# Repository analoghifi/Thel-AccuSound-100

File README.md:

# Thel AccuSound 100
Thel AccuSound 100 audio power amplifier module (mono single channel)  
using vertical MOSFETs (often generalised as "[HEXFET](https://sound-au.com/articles/hexfet.htm)s")
* RMS power output from 20W up to 500W\* (1000W\*\*) | 7Hz...1,5MHz [-3dB]  |  0,4µs
* Class-A-Mode possible | Bridge Mode possible  
* unbalanced (single-ended/asymmetrical) audio input  
* not DC-coupled (has an input Cap (KP film/foil))  
* using vertical MOSFETs IRFP240 / IRFP9240  
* integrated (DC-) protection & anti-pop delay -circuit with relays
  
\*(depends on the supply voltage only)  
\*\*(bridge mode and short time only ➔ see <a href="/docs/4.) final version 2003-2015/power_output_table_version_2003-2015.png">Table 1</a> / <a href="/docs/3) version 1995-2003/power_output_table_version_1995-2003__V2.jpg">Table 2</a>)  
  
#### changes from "3) version 1995-2003" *[AccuSound Pro]* to "4) final version 2003-2015" *[AccuSound 100]*:  
* introducing source resistors (for better stability / better thermal behaviour / better currenct and load sharing)
* therefore reduced power output (compare <a href="/docs/3) version 1995-2003/power_output_table_version_1995-2003__V2.jpg">old</a> with <a href="/docs/4.) final version 2003-2015/power_output_table_version_2003-2015.png">new</a>)
* slightly different schematic (compare <a href="/hardware/3) version 1995-2003/accusound_version_1995-2003_schematic_V1.jpg">old</a> with <a href="/hardware/4.) final version 2003-2015/AccuSound_100_schematic_2004__corrected.jpg">new</a>)
* different pcb layout
* in the middle of 2010: replacement of the 2 very good tungsten-silver double (two-step)\*\*\* contact relays (erosion-resistant) with 2 normal "high-current" relays (Schrack RP3SL024)  
* replacing almost all foil caps (including the input cap) with the very good CDE film/foil KP-caps (<a href="https://github.com/analoghifi/capacitors/blob/main/audio%20and%20filter%20capacitors/docs/datasheets/kp/CDE_series_WPP.pdf">WPP-Series</a>)
* introducing silver mica bypass caps at some sensible places in the circuit
  
\*\*\*(see here -> <a href="/docs/components datasheets/special relay version 1995-2003">Relay type: Hengstler H-550-1759"</a>)
  
.
  
## last 4.x) version sold from 2003 til 2015:  

https://web.archive.org/web/20071014012558/http://www.thel-audioworld.de/module/acuso/acuso.htm  
https://web.archive.org/web/20120130132153/http://thel-audioworld.de/module/acuso/acuso.htm  
https://web.archive.org/web/20150216004915/http://www.thel-audioworld.de/module/acuso/acuso.htm  
  
## older 3) version sold from 1995 til 2003:  

https://web.archive.org/web/20020608091959/http://thel-audioworld.de:80/module/acuso/acuso.htm  

----  
### Kicad projects in this repo:  
* [version 2006-2011](https://github.com/analoghifi/Thel-AccuSound-100/tree/main/hardware/4.\)%20final%20version%202003-2015/4.2\)%20version%202006-2011/KiCad/original) | state: initial release v1.01 | like the original, 1-layer, THT
* [version 2011-2015](https://github.com/analoghifi/Thel-AccuSound-100/tree/main/hardware/4.\)%20final%20version%202003-2015/4.3\)%20version%202011-2015/KiCad/original) | state: coming soon... | like the original, 1-layer, THT

----

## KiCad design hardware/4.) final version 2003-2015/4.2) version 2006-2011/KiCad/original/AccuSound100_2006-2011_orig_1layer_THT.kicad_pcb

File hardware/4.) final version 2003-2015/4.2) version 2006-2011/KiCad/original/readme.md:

#### work in progress not finished yet !  

this is not the original Thel PCB but it's very like\* the original with the following exceptions:  
* different board dimensions original: 200mm x 100mm -> this PCB: 200mm x 103mm  
* using a combined 5.0mm/7.5mm pin spacing footprint for the small foil caps C12 and C23
* using a combined 3.5mm/5.0mm/5.9mm/7.5mm pin spacing footprint for the Mica caps C2, C3 and C9 (see below)  
  
\*(same schematic / same 1-layer\** layout THT / same THT components in the same places on the board)  
\**(strictly speaking, this KiCad PCB is a two-layer PCB with plated-through holes, but you can also (let) produce it as a classic 1-layer PCB with non-plated holes if you wish, since all the tracks are on the bottom side only)  
  
----  

### remarks:  
#### C2,C3,C9: 
in the original, Mica capacitors from the US company "Cornell Dubilier Electronics" (CDE) are used for C2, C3 and C9  
the [CD15-Series](https://github.com/analoghifi/capacitors/blob/main/audio%20and%20filter%20capacitors/docs/datasheets/mica%20glimmer/CDE_Silver_Mica_series_STD-DIPPED.pdf) or the better [CD17 Series](https://github.com/analoghifi/capacitors/blob/main/audio%20and%20filter%20capacitors/docs/datasheets/mica%20glimmer/CDE_Series_CD17_CD18_high_frequency.pdf) is used:  
* C2, C3 = 47pF / 1% / 500V / 5.9mm pitch / Type-No. CD15ED470FO3 ([stock at Mouser](https://www2.mouser.com/ProductDetail/Cornell-Dubilier-CDE/CD15ED470FO3?qs=9iVfQKk8ifFmXLRqX5bCNQ%3D%3D))  
or better CD17ED470JO3F ([stock at Mouser](https://www2.mouser.com/ProductDetail/Cornell-Dubilier-CDE/CD17ED470JO3F?qs=nnhpPVbCybXjnSWSlsUlRA%3D%3D))
* C9 = 10pF / 5% / 500V / 5.9mm pitch / Type-No. CD15CD100JO3 ([stock at Mouser](https://www2.mouser.com/ProductDetail/Cornell-Dubilier-CDE/CD15CD100JO3?qs=m9iv7GyUMnFXRIC2%252BbnrrQ%3D%3D))  
or better CD17CD100JO3F ([stock at Mouser](https://www2.mouser.com/ProductDetail/Cornell-Dubilier-CDE/CD17CD100JO3F?qs=PXF%252Blbo4VJ7Sv5GDGZWsoQ%3D%3D))

Alternatively:  
since C2,C3 and C9 are used for controlling the ultrasonic frequencies (>20kHz) here in this circuit you may use instead  
ceramic C0G capacitors (tolerance: 1% to 2,5% / rated DC Voltage: 100V or 250V / pitch 5mm or 7,5mm)  
e.g. KEMET "[goldmax 300](https://github.com/analoghifi/capacitors/blob/main/audio%20and%20filter%20capacitors/docs/datasheets/C0G/KEMET_C1049_GOLDMAX_C0G_THT.pdf)" Series in THT version ([10pF/47pF stock at mouser](https://www2.mouser.com/c/passive-components/capacitors/ceramic-capacitors/mlccs-multilayer-ceramic-capacitors/multilayer-ceramic-capacitors-mlcc-leaded/?q=goldmax&capacitance=10%20pF%7C~47%20pF&dielectric=C0G%20%28NP0%29&lead%20spacing=5.08%20mm&tolerance=1%20%25&voltage%20rating%20dc=250%20VDC))  
They perform very well for high frequencies and are a very good alternative to the expensive Mica caps from CDE.  
The dielectric material is important here: Do NOT use ceramic capacitors with a dielectric other than C0G (NP0) !  
  
The footprint on my PCB is prepared for both pitches:  
the odd 5.9mm for the Micas as well as 3.5mm / 5.0mm or 7.5mm for alternative capacitors  
 
----  
  
these are KiCad 6.x projects  
see how to get the proper 3D-Models from here: https://github.com/analoghifi/KiCad-3D-Models  
  
----  
  
use kicanvas.org to see this KiCad-Project in Browser:  
https://kicanvas.org/?github=https://github.com/analoghifi/Thel-AccuSound-100/tree/main/hardware/4.)%20final%20version%202003-2015/4.2)%20version%202006-2011/KiCad/original

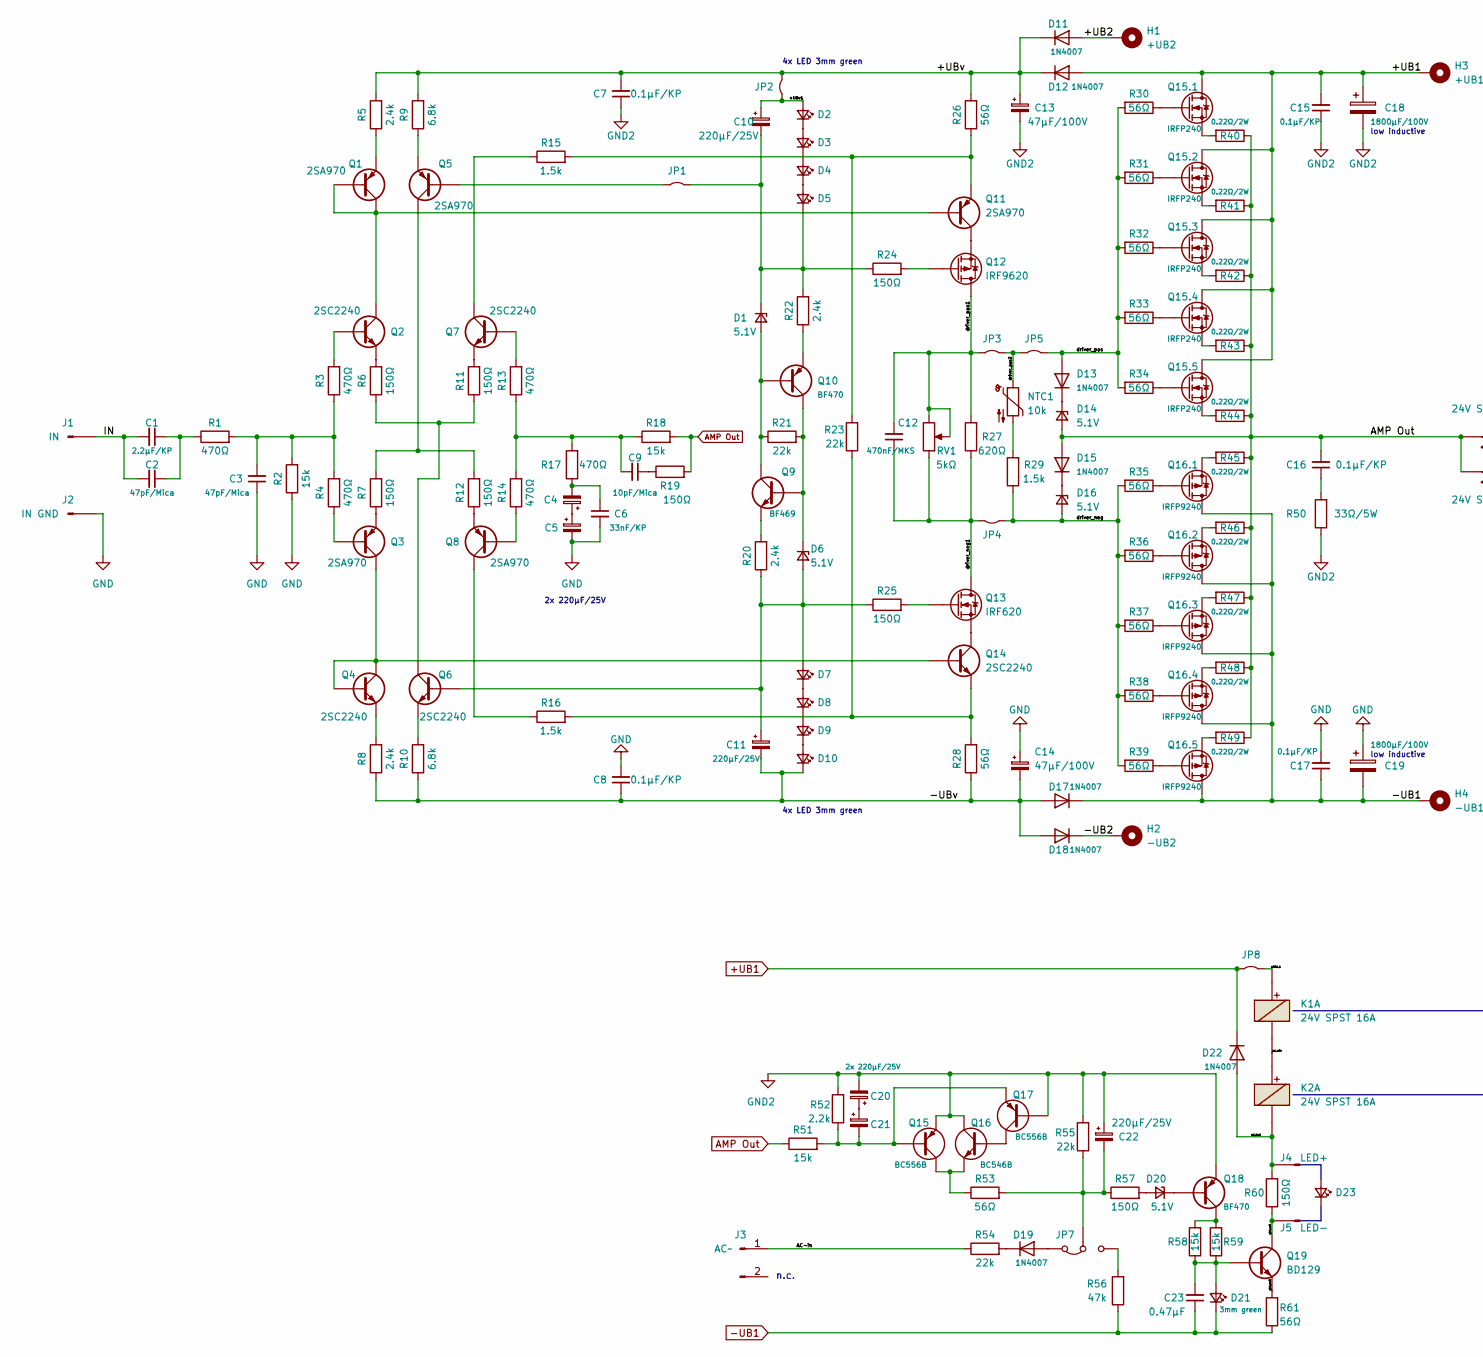
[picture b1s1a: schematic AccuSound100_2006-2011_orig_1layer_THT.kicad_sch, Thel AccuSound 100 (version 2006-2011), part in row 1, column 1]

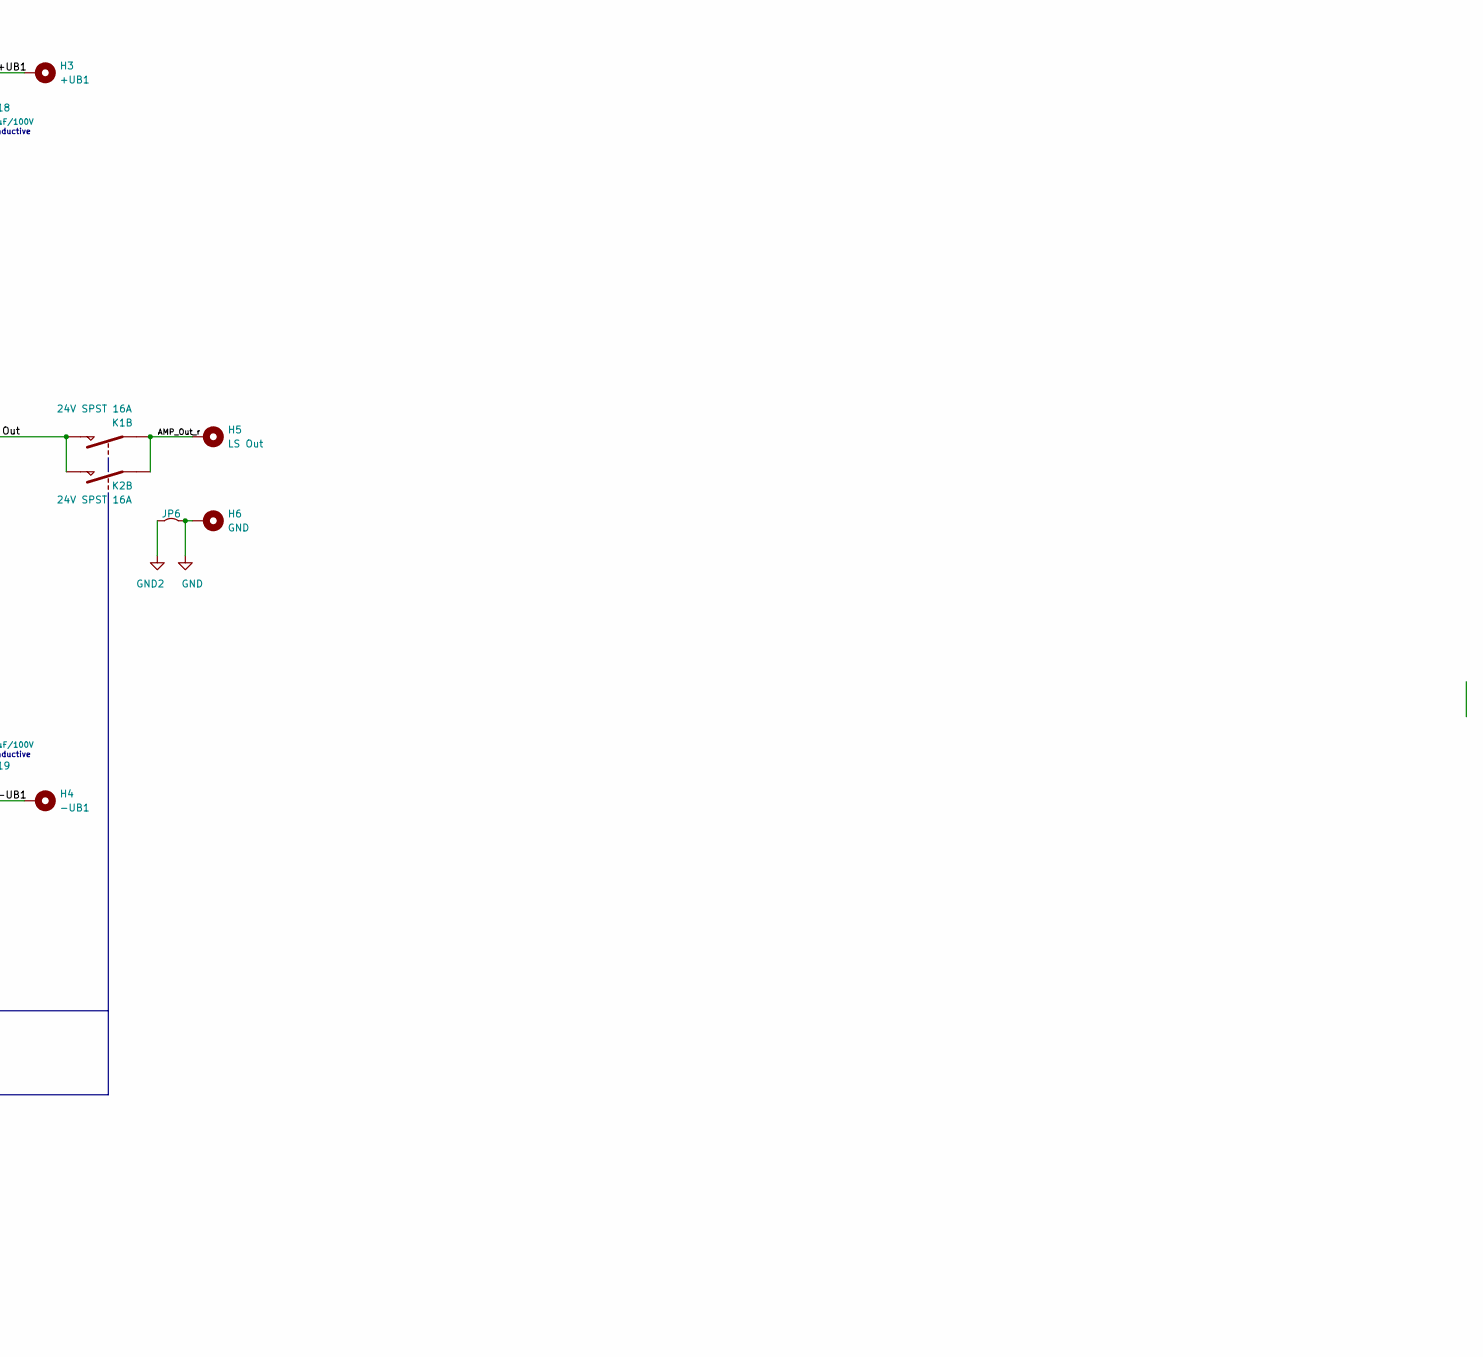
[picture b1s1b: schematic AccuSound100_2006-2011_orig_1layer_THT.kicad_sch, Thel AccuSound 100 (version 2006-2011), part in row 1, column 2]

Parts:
C1: 2.2µF/KP; C_Axial_L42mm_D22mm_P45mm_Horizontal
C2, C3: 47pF/Mica; C_Rect_Mica_Multi_L11.0mm_W3.5mm_P3.50_P5.00_P5.90_P7.50mm
C4, C5, C10, C11, C21, C22: 220µF/25V; CP_Radial_Black_D8.2mm_H12.0mm_P3.50mm_minimal_silk
C6: 33nF/KP; C_Tower_EMZ_small_medium
C7, C8, C15, C16, C17: 0.1µF/KP; C_Axial_L27mm_D9mm_P27.5mm_Horizontal
C9: 10pF/Mica; C_Rect_Mica_Multi_L11.0mm_W3.5mm_P3.50_P5.00_P5.90_P7.50mm
C12: 470nF/MKS; C_Rect_L10.0mm_W4.0mm_P5.00_P7.50mm
C13, C14: 47µF/100V; CP_Radial_D10.0mm_H12.5mm_P5.00mm_minmal_silk
C18, C19: 1800µF/100V; CP_Radial_D26.0mm_P10.00mm_SnapIn
C20: 2x 220µF/25V; CP_Radial_Black_D8.2mm_H12.0mm_P3.50mm_minimal_silk
C23: 0.47µF; C_Rect_L10.0mm_W4.0mm_P5.00_P7.50mm
D1, D6, D20: 5.1V; D_DO-41_SOD81_very_long_P12.7mm_Horizontal_minSilk
D2, D5, D7, D8, D10, D23: LED_Small; LED_D3.0mm
D3, D4, D9: LED_Small; LED_D3.0mm_medium_P3.5mm
D11, D12: 1N4007; Diode_long_L6.3mm_D2.5mm_P11,43mm_Horizontal_minSilk
D13: 1N4007; Diode_L6.3mm_D2.5mm_P10.16mm_Horizontal_minSilk
D14: 5.1V; D_DO-41_SOD81_short_P9.0mm_Horiz_minSilk
D15: 1N4007; Diode_short_L6.3mm_D2.5mm_P9mm_Horizontal_minSilk
D16: 5.1V; D_DO-41_SOD81_P10.16mm_Horizontal_minSilk
D17, D18, D19: 1N4007; Diode_long_L6.3mm_D2.5mm_P12.7mm_Horizontal_minSilk
D21: 3mm green; LED_D3.0mm
D22: 1N4007; D_DO-41_SOD81_very_short_P7.62mm_Horiz_minSilk
H1: +UB2; MountingHole_4.3mm_M4_big_Pad_TopBottom
H2: -UB2; MountingHole_4.3mm_M4_big_Pad_TopBottom
H3: +UB1; MountingHole_4.3mm_M4_big_Pad_TopBottom
H4: -UB1; MountingHole_4.3mm_M4_big_Pad_TopBottom
H5: LS Out; MountingHole_4.3mm_M4_big_Pad_TopBottom
H6: GND; MountingHole_4.3mm_M4_big_Pad_TopBottom
J1: IN; Loet_Pin_D1.5mm_L14.0mm
J2: IN GND; Loet_Pin_D1.5mm_L14.0mm
J3: AC~; PinHeader_1x02_P2.54mm_Vertical
J4: LED+; Loet_Pin_D1.5mm_L14.0mm
J5: LED-; Loet_Pin_D1.5mm_L14.0mm
JP1, JP3: Jumper_2_Bridged; R_Axial_long_L6.3mm_D2.5mm_P11.43mm_Horizontal_minSilk
JP2, JP4, JP8: Jumper_2_Bridged; R_Axial_very_long_L6.3mm_D2.5mm_P12.7mm_Horizontal_minSilk
JP5: Jumper_2_Bridged; R_Axial_even_longer_L6.3mm_D2.5mm_P13.2mm_Horizontal_minSilk
JP6: Jumper_2_Bridged; bridge_Wire-1.5mm_diameter
JP7: Jumper_3_Bridged12; PinHeader_1x03_P2.54mm_Vertical
K1, K2: 24V SPST 16A; Relay_SPST_Schrack-RM5mm
NTC1: 10k; Pads_for_NTC_P3mm
Q1, Q8: 2SA970; TO-92
Q2, Q4, Q7: 2SC2240; TO-92
Q3, Q5: 2SA970; TO-92_wide
Q6, Q14: 2SC2240; TO-92_wide
Q9: BF469; TO-126-3_Vertical
Q10, Q18: BF470; TO-126-3_Vertical
Q11: 2SA970; TO-92_Wide
Q12: IRF9620; TO-220-3_Vertical
Q13: IRF620; TO-220-3_Vertical
Q15, Q17: BC556B; TO-92_wide
Q15.1, Q15.2, Q15.3, Q15.4, Q15.5: IRFP240; TO-247-3_Horizontal_TabDown_short
Q16: BC546B; TO-92_wide
Q16.1, Q16.2, Q16.3, Q16.4, Q16.5: IRFP9240; TO-247-3_Horizontal_TabDown_short
Q19: BD129; TO-126-3_Vertical
R1, R3, R4, R13, R14, R17: 470Ω; R_Axial_very_long_L6.3mm_D2.5mm_P12.7mm_Horizontal_minSilk
R2, R18, R51, R58, R59: 15k; R_Axial_very_long_L6.3mm_D2.5mm_P12.7mm_Horizontal_minSilk
R5, R8, R20, R22: 2.4k; R_Axial_very_long_L6.3mm_D2.5mm_P12.7mm_Horizontal_minSilk
R6, R7, R11, R12, R19, R25, R57, R60: 150Ω; R_Axial_very_long_L6.3mm_D2.5mm_P12.7mm_Horizontal_minSilk
R9, R10: 6.8k; R_Axial_very_long_L6.3mm_D2.5mm_P12.7mm_Horizontal_minSilk
R15, R29: 1.5k; R_Axial_very_long_L6.3mm_D2.5mm_P12.7mm_Horizontal_minSilk
R16: 1.5k; R_Axial_DIN0207_L6.3mm_D2.5mm_P10.16mm_Horizontal_minSilk
R21, R23, R54, R55: 22k; R_Axial_very_long_L6.3mm_D2.5mm_P12.7mm_Horizontal_minSilk
R24: 150Ω; R_Axial_DIN0207_L6.3mm_D2.5mm_P10.16mm_Horizontal_minSilk
R26, R28, R31, R32, R33, R34, R35, R36, R37, R38, R53, R61: 56Ω; R_Axial_very_long_L6.3mm_D2.5mm_P12.7mm_Horizontal_minSilk
R27: 620Ω; R_Axial_Short_L6.3mm_D2.5mm_P9.0mm_Horiz_minSilk
R30, R39: 56Ω; R_Axial_long_L6.3mm_D2.5mm_P11.43mm_Horizontal_minSilk
R40, R41, R42, R43, R44, R45, R46, R47, R48, R49: 0.22Ω/2W; R_Box_L13.0mm_W4.0mm_P9.00mm
R50: 33Ω/5W; R_Axial_DIN0918_L18mm_D9mm_P22mm_Horizontal
R52: 2.2k; R_Axial_very_long_L6.3mm_D2.5mm_P12.7mm_Horizontal_minSilk
R56: 47k; R_Axial_very_long_L6.3mm_D2.5mm_P12.7mm_Horizontal_minSilk
RV1: 5kΩ; Potentiometer_Bourns_3386P_Vertical

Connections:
+UB1: C15.2, C18.1, D12.2 (A), D22.1 (K), H3.1, JP8.1 (A), Q15.1.2 (D), Q15.2.2 (D), Q15.3.2 (D), Q15.4.2 (D), Q15.5.2 (D)
-UB1: C17.1, C19.2, C23.1, D17.1 (K), D21.1 (K), H4.1, Q16.1.2 (D), Q16.2.2 (D), Q16.3.2 (D), Q16.4.2 (D), Q16.5.2 (D), R56.1, R61.1
/+UB1_1: JP8.2 (B), K1.A1
/+UB2: D11.2 (A), H1.1
/+UBv: C7.2, C13.1, D11.1 (K), D12.1 (K), JP2.2 (B), R5.2, R9.2, R26.2
/+UBv1: C10.1, D2.2 (A), JP2.1 (A)
/-UB2: D18.1 (K), H2.1
/-UBv: C8.1, C11.2, C14.2, D10.1 (K), D17.2 (A), D18.2 (A), R8.1, R10.1, R28.1
/AC-in: J3.1, R54.1
/AMP_Out_r: H5.1, K1.11, K2.11
/IN: C1.2, C2.2, J1.1
/driver_neg: D16.2 (A), JP4.1 (A), R29.1, R35.2, R36.2, R37.2, R38.2, R39.2
/driver_neg1: C12.1, JP4.2 (B), Q13.2 (D), R27.1, RV1.1
/driver_pos: D13.2 (A), JP5.2 (B), R30.2, R31.2, R32.2, R33.2, R34.2
/driver_pos1: C12.2, JP3.1 (A), Q12.2 (D), R27.2, RV1.2, RV1.3
/driver_pos2: JP3.2 (B), JP5.1 (A), NTC1.1
/q19_coll: J5.1, Q19.2 (C), R60.1
/q19_emit: Q19.1 (E), R61.2
/rel_foot: D22.2 (A), J4.1, K2.A2, R60.2
/rel_mid: K1.A2, K2.A1
AMP Out: C16.2, D14.2 (A), D15.2 (A), K1.14, K2.14, R18.2, R19.2, R40.1, R41.1, R42.1, R43.1, R44.1, R45.1, R46.1, R47.1, R48.1, R49.1, R51.1
GND: C3.1, C5.2, C6.2, C8.2, C14.1, C17.2, C19.1, H6.1, J2.1, JP6.2 (B), R2.1
GND2: C7.1, C13.2, C15.1, C18.2, C20.2, C22.1, JP6.1 (A), Q15.3 (E), Q16.1 (C), Q17.2 (B), Q18.1 (E), R50.1, R52.2, R55.2
unnamed: C1.1, C2.1, R1.1
unnamed: C3.2, R1.2, R2.2, R3.1, R4.2
unnamed: C4.1, C5.1
unnamed: C4.2, C6.1, R17.1
unnamed: C9.1, R19.1
unnamed: C9.2, R13.1, R14.2, R17.2, R18.1
unnamed: C10.2, D1.1 (K), D5.1 (K), JP1.2 (B), R22.2, R24.1
unnamed: C11.1, D6.2 (A), D7.2 (A), Q6.3 (B), R20.1, R25.1
unnamed: C16.1, R50.2
unnamed: C20.1, C21.1
unnamed: C21.2, Q15.2 (B), Q17.3 (E), R51.2, R52.1
unnamed: C22.2, JP7.2 (C), R53.2, R55.1, R57.1
unnamed: C23.2, D21.2 (A), Q19.3 (B), R58.1, R59.1
unnamed: D1.2 (A), Q9.2 (C), Q10.3 (B), R21.1
unnamed: D2.1 (K), D3.2 (A)
unnamed: D3.1 (K), D4.2 (A)
unnamed: D4.1 (K), D5.2 (A)
unnamed: D6.1 (K), Q9.3 (B), Q10.2 (C), R21.2
unnamed: D7.1 (K), D8.2 (A)
unnamed: D8.1 (K), D9.2 (A)
unnamed: D9.1 (K), D10.2 (A)
unnamed: D13.1 (K), D14.1 (K)
unnamed: D15.1 (K), D16.1 (K)
unnamed: D19.1 (K), R54.2
unnamed: D19.2 (A), JP7.1 (A)
unnamed: D20.1 (K), Q18.3 (B)
unnamed: D20.2 (A), R57.2
unnamed: JP1.1 (A), Q5.3 (B)
unnamed: JP7.3 (B), R56.2
unnamed: NTC1.2, R29.2
unnamed: Q1.1 (E), R5.1
unnamed: Q1.2 (C), Q1.3 (B), Q2.2 (C), Q11.3 (B)
unnamed: Q2.1 (E), R6.2
unnamed: Q2.3 (B), R3.2
unnamed: Q3.1 (E), R7.1
unnamed: Q3.3 (B), R4.1
unnamed: Q4.1 (E), R8.2
unnamed: Q5.1 (E), R9.1
unnamed: Q5.2 (C), R7.2, R12.2
unnamed: Q6.1 (E), R10.2
unnamed: Q6.2 (C), R6.1, R11.1
unnamed: Q7.1 (E), R11.2
unnamed: Q7.2 (C), R15.1
unnamed: Q7.3 (B), R13.2
unnamed: Q8.1 (E), R12.1
unnamed: Q8.2 (C), R16.1
unnamed: Q8.3 (B), R14.1
unnamed: Q9.1 (E), R20.2
unnamed: Q10.1 (E), R22.1
unnamed: Q11.1 (E), R15.2, R23.2, R26.1
unnamed: Q11.2 (C), Q12.3 (S)
unnamed: Q12.1 (G), R24.2
unnamed: Q13.1 (G), R25.2
unnamed: Q13.3 (S), Q14.2 (C)
unnamed: Q14.1 (E), R16.2, R23.1, R28.2
unnamed: Q3.2 (C), Q4.2 (C), Q4.3 (B), Q14.3 (B)
unnamed: Q15.1 (C), Q16.3 (E), R53.1
unnamed: Q15.1.1 (G), R30.1
unnamed: Q15.1.3 (S), R40.2
unnamed: Q15.2.1 (G), R31.1
unnamed: Q15.2.3 (S), R41.2
unnamed: Q15.3.1 (G), R32.1
unnamed: Q15.3.3 (S), R42.2
unnamed: Q15.4.1 (G), R33.1
unnamed: Q15.4.3 (S), R43.2
unnamed: Q15.5.1 (G), R34.1
unnamed: Q15.5.3 (S), R44.2
unnamed: Q16.2 (B), Q17.1 (C)
unnamed: Q16.1.1 (G), R35.1
unnamed: Q16.1.3 (S), R45.2
unnamed: Q16.2.1 (G), R36.1
unnamed: Q16.2.3 (S), R46.2
unnamed: Q16.3.1 (G), R37.1
unnamed: Q16.3.3 (S), R47.2
unnamed: Q16.4.1 (G), R38.1
unnamed: Q16.4.3 (S), R48.2
unnamed: Q16.5.1 (G), R39.1
unnamed: Q16.5.3 (S), R49.2
unnamed: Q18.2 (C), R58.2, R59.2

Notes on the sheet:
4x LED 3mm green
n.c.
low inductive
2x 220µF/25V

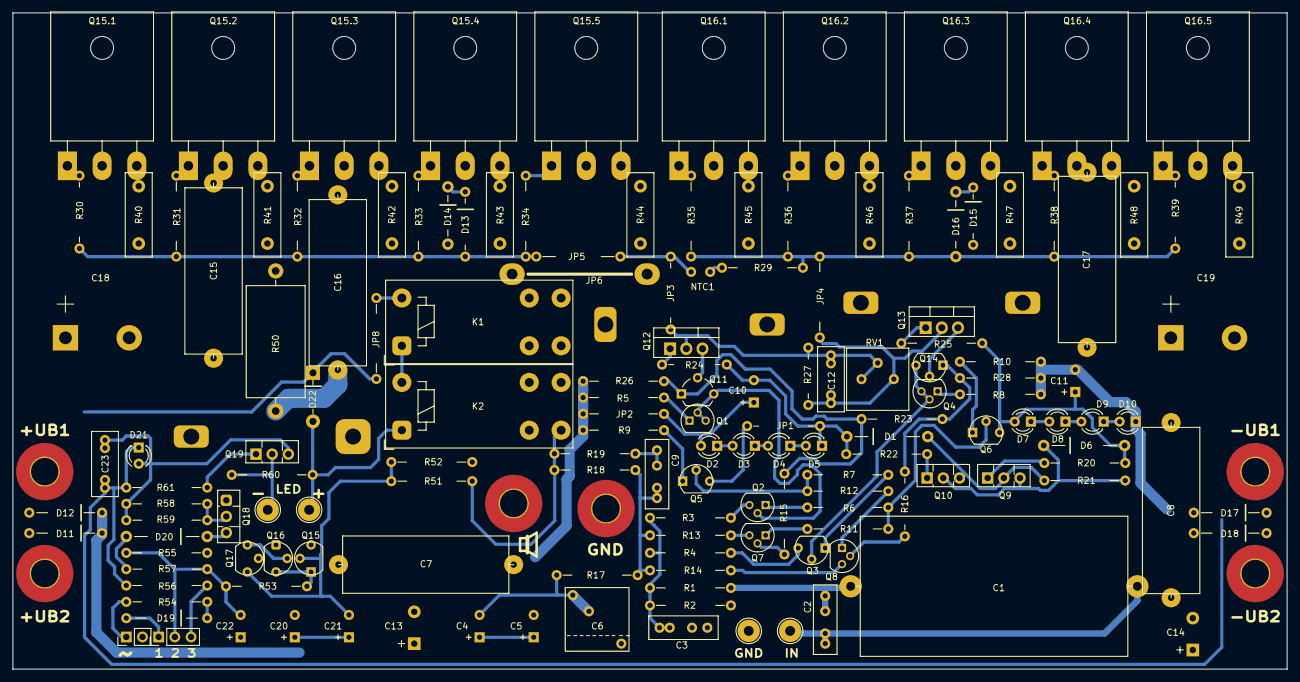
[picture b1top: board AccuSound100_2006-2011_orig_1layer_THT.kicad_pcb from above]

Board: 2 copper layers, 200.0 x 103.0 mm, 158 parts (0 on the bottom side), 102 nets.
